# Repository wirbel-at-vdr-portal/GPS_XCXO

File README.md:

# About
Project goal is a small budget hobbyists GPS disciplined 10MHz XCXO with less than 0.01Hz freq offset at 10MHz using a GPS receiver with 1PPS output.

# Ingredients
- an cheap 10MHz OCXO with 0..4 volts V_control input, which has in it's voltage control range the center freq of 10.000000 MHz and CMOS or TTL output,
  costs at common market places ~15€. I use an CTI OSC5A2B02 OCXO based board. It needs to be modified however, to have a control voltage input instead of a potentiometer.
- an ESP32 devkit C V4, ~12€ (mine was ~8€)
- Arduino IDE with a few libs, 0€, but some efforts in/plus time/research.
- a GPS module with an 1 pulse per second output, in my case
  - Sparkfun GPS-17285 module (Neo-M9N)
  - Sparkfun GPS-14986 antenna
- a few electronic components
- an old 1.8 inch TFT based on St7735, i use the one with the large SD card slot, ~6€
- the PCB, design is here, ~25€ for 5 pieces.
- a 9..12volts DC power supply with ~1amp continously, - no costs. Everybody has such one laying around. Preferred with the 5.5mm 'DC connector', plus is inner.

# How it is working

- the 1PPS signal from the GNSS / GPS module triggers an interrupt routine, which resets a counter.
- the 10MHz signal is counted by the ESP32 specific hardware counter PCNT. Every 30000 counts, this counter fires a second ISR to count it's overflows.
  This ISR is called 333 times a second.
- if the gate time is over, we remember the current counter value (0..29999) as 'last_counter' and calculate the number of pulses: pulses = current_counter + overflows * 30000 - last_counter
- now, we can calculate the frequency: frequency = pulses / gate_time
- and the current frequency error in ppb: errorPPB = (measuredFreq - TARGET_FREQ) / (TARGET_FREQ / 1e9)
- as our OCXO is voltage controlled by 0..4volts, we need to generate a control voltage. We generate a 16-bit PWM, again using hardware counters of the ESP32.
- the pwm signal is RC filtered, we need to put a bit effort in this filter. We want more than 120dB frequency suppression for the PWM frequency.
- and finally, we somehow need to map an error in ppb to an PWM value. This job serves a digital filter with a bit brain, the Kalman filter.
- if the OCXO is learned, the program stores from time to time the current state

# Modification of the OCXO board
My OCXO board doesnt have a control voltage input. Instead, the input is wired to a potentiometer. The modified circuit is shown below.

NOTE: the original schematic was not done by me, see doc folder for original.

# Performance
- for my system, which is a very early breadboard-like assembly
- the algorithm needs time to adapt the OCXO, learn it's properties, so it's slow. Don't expect good results in less than two hours.
- there are still plenty of knobs to tune
- we need the OCXO control signal as clean as possible, so shielding and good RC filtering is mandatory.
- TODO
  - improve GPS quality (cheap module)
  - tune code, if GPS loss or invalid values.

| Running hh:mm:ss | abs(FreqOffset), Hz | PWM change 0..65535 | Uncertainty | comment |
| ----------- | ---------------- | ---------- | ----------- | -------- |
| 00:00:10    | 2.9              | 4751       | 490.8       |          |
| 00:00:20    | 1.8              | 2949       | 947.4       |          |
| 00:02:00    | 1.65             | 2703       | 264.0       |          |
| 00:03:40    | 0.51             |  836       | 205.7       |          |
| 00:12:00    | 0,216            |  354       |  10.7       |          |
| 00:28:40    | 0.058            |   95       |   2.65      |          |
| 00:45:20    | 0.013            |   21       |   2.31      |          |
| 01:02:00    | 0.002            |    3       |   1.9982    |          |
| 01:18:40    | 0.040            |    7       |   1.726     | GPS err  |
| 01:18:50    | 0                |    0       |   3.4488    | algo!    |
| 01:35:30    | 0.002            |    3       |   1.8489    | recover  |
| 01:52:10    | 0.001            |    2       |   1.3932    |          |

***NOTE NOTE NOTE:***

***This is work in progress. Everything still changes day by day. Success is optional, this is a fully fun based project.***

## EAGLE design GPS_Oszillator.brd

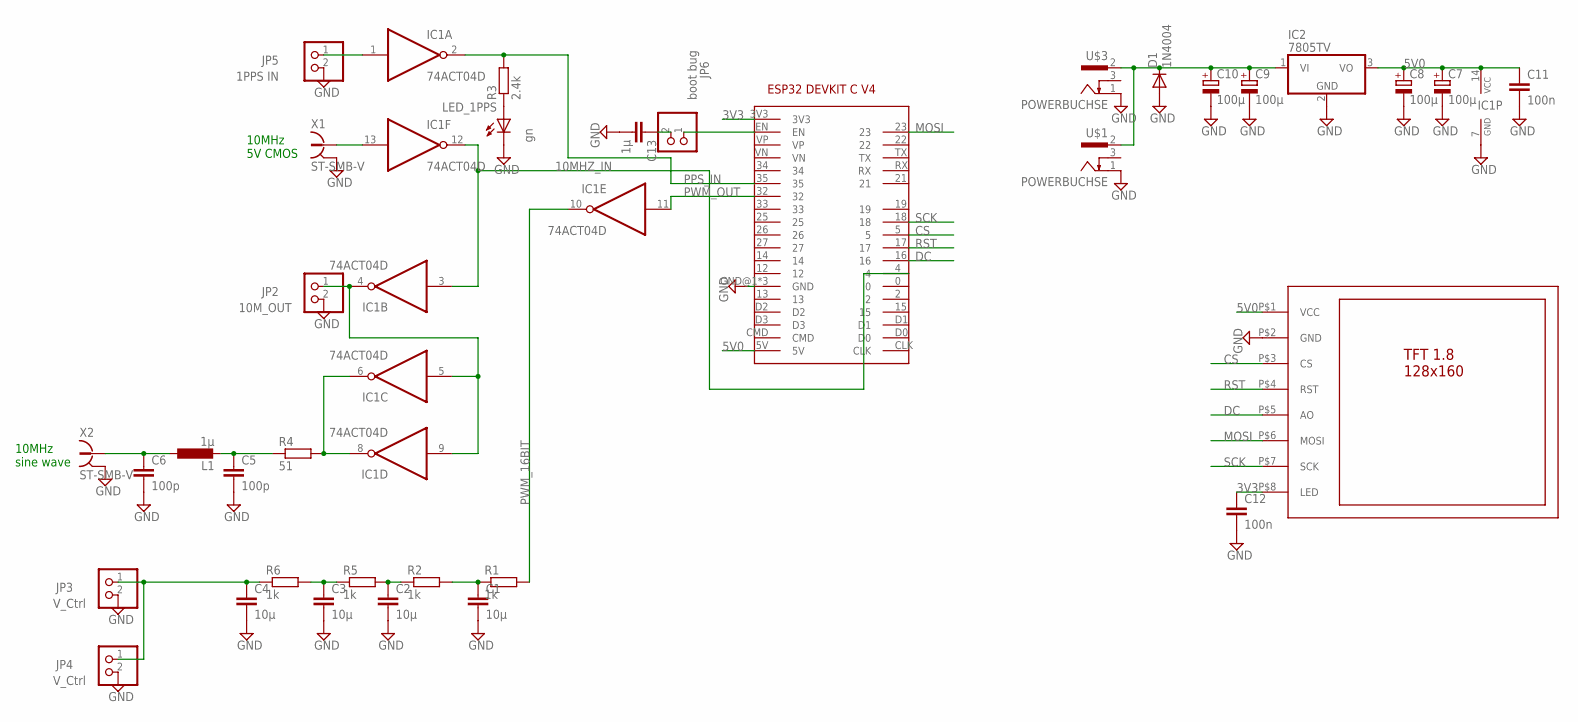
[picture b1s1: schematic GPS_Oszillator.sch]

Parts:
C1, C2, C3, C4: 10µ; C1206
C5, C6: 100p; C0805
C7, C8, C9, C10: 100µ; SANYO-OSCON_SMD_E7
C11, C12: 100n; C0805
C13: 1µ; C1210
D1: 1N4004; DO41-10
IC1: 74ACT04D; SO14
IC2: 7805TV; TO220V
JP2: 10M_OUT; 1X02
JP3, JP4: V_Ctrl; 1X02
JP5: 1PPS IN; 1X02
JP6: boot bug; 1X02
L1: 1µ; L1812
LED_1PPS: gn; CHIPLED_0805
R1, R2, R5, R6: 1k; R0805
R3: 2.4k; R0805
R4: 51; R0805
U$1, U$3: POWERBUCHSE
U$2: TFT_18
U$4: ESP32_DEVKITC_V4; ESP32_DEVKIT_C_V4
X1, X2: ST-SMB-V

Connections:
3V3: C12.1, U$2.P$8 (LED), U$4.3V3
5V0: C7.+, C8.+, C11.1, IC1.14 (VCC), IC2.3 (VO), U$2.P$1 (VCC), U$4.5V
10MHZ_IN: IC1.3 (I), IC1.12 (O), U$4.4
CS: U$2.P$3 (CS), U$4.5
DC: U$2.P$5 (AO), U$4.16
ESP32_EN: JP6.1, U$4.EN
GND: C1.2, C2.2, C3.2, C4.2, C5.2, C6.2, C7.-, C8.-, C9.-, C10.-, C11.2, C12.2, C13.2, D1.A, IC1.7 (GND), IC2.2 (GND), JP2.2, JP3.2, JP4.2, JP5.2, LED_1PPS.C, U$1.1 (2), U$2.P$2 (GND), U$3.1 (2), U$4.GND@1 (GND), U$4.GND@2 (GND), U$4.GND@3 (GND), X1.2, X1.3 (2), X1.4 (2), X1.5 (2), X2.2, X2.3 (2), X2.4 (2), X2.5 (2)
MOSI: U$2.P$6 (MOSI), U$4.23
unnamed: C3.1, R5.1, R6.2
unnamed: IC1.4 (O), IC1.5 (I), IC1.9 (I), JP2.1
unnamed: C2.1, R2.1, R5.2
unnamed: C13.1, JP6.2
unnamed: C1.1, R1.1, R2.2
unnamed: C4.1, JP3.1, JP4.1, R6.1
unnamed: IC1.1 (I), JP5.1
unnamed: LED_1PPS.A, R3.1
unnamed: C6.1, L1.1, X2.1
unnamed: C5.1, L1.2, R4.1
unnamed: IC1.6 (O), IC1.8 (O), R4.2
unnamed: C9.+, C10.+, D1.C, IC2.1 (VI), U$1.2 (1), U$3.2 (1)
unnamed: IC1.13 (I), X1.1
PPS_IN: IC1.2 (O), R3.2, U$4.35
PWM_16BIT: IC1.10 (O), R1.2
PWM_OUT: IC1.11 (I), U$4.32
RST: U$2.P$4 (RST), U$4.17
SCK: U$2.P$7 (SCK), U$4.18

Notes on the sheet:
10MHz 5V CMOS
10MHz sine wave

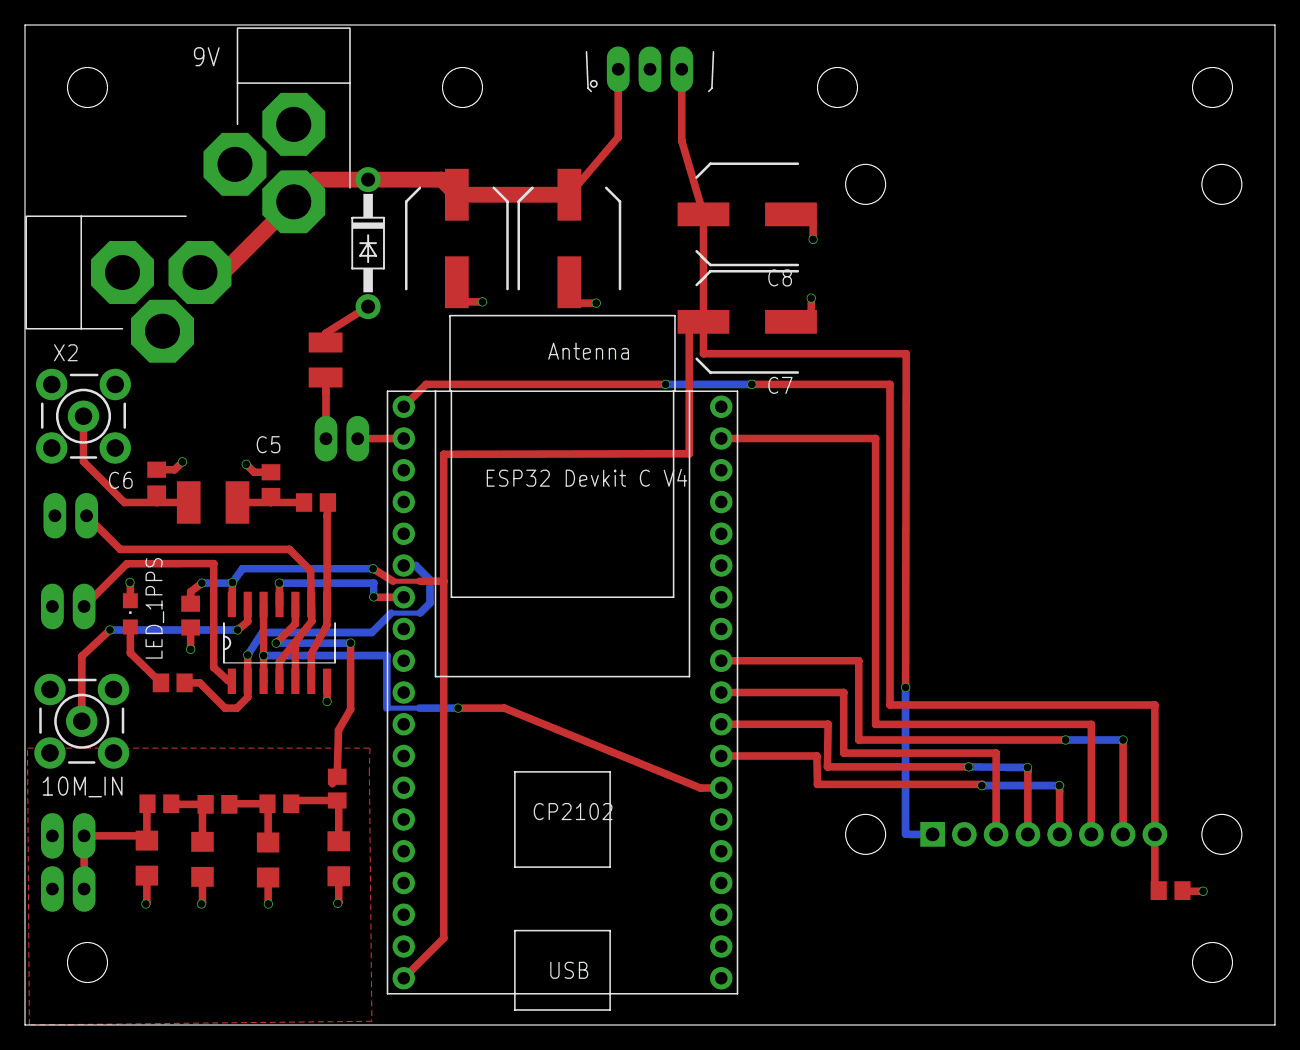
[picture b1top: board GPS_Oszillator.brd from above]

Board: 2 copper layers, 100.0 x 80.0 mm, 35 parts (0 on the bottom side), 26 nets.

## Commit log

2026-04-26 Add project goal to README.md
2026-04-27 Expand README with project details and ingredients
    Added project ingredients and notes about progress.
2026-04-29 Enhance README notes and thoughts formatting
    Updated the note section for clarity and emphasis. Reformatted thoughts for better readability.
2026-04-30 Change PWM filter
2026-05-02 Add first version of an Kalman Filter
    A Kalman filter is an iterative mathematical algorithm used to optimally estimate the state of a dynamic system (such as position or velocity) from a series of measurement errors. It was introduced b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
2026-05-02 Revise README for clarity and project details
    Updated project description and ingredients list for clarity. Added planned functionality and notes on project progress.
2026-05-02 Revise GPS module details in README
    Updated GPS module description and pricing.
2026-05-02 Fix typo in README regarding pulse calculation
2026-05-02 Update PWM generation description in README
2026-05-02 Update README with completed thoughts
    Strikethrough completed thoughts in README.
2026-05-02 fix folder structure
2026-05-02 update esp32 inputs.
2026-05-03 add second power connector and sort out drc errors
2026-05-04 add filter comparison in LTspice
2026-05-04 fix PCNT initialization and dont reset PCNT
    1. fix new initialization of PCNT Driver (v5.x) -> .low_limit = -1
    2. dont reset interrupt in OnOverflow(), just count.
    3. dont reset PCNT to zero in OnPPS() anymore. Instead, remember it's start value in loop(). This increases the counter accuracy.
    4. clean code.
2026-05-04 Increase accuracy of filter
    1. use double, instead of float in Kalman filter.
    2. begin playing with tuning variables
    3. add 1000sec measurement time
2026-05-05 save current setup.
2026-05-06 Revise README with updated project specifications
    Updated project details and specifications in README.md. Modified ingredient costs and clarified the working mechanism of the system.
2026-05-06 Enhance README with performance insights and TODOs
    Added performance section with details on OCXO adaptation and tuning.
2026-05-06 Add image to README and update project status note
2026-05-06 save current state
2026-05-08 Update project goal
    Updated project goal to specify a frequency offset of less than 0.01Hz instead of 0.5Hz.
2026-05-08 Update ingredients
2026-05-08 Update frequency calculation details
2026-05-08 Clarify counting process and ISR in README
    Refined explanation of the counting process and ISR calls.
2026-05-08 add image
    Added an image to the README and clarified project details.
2026-05-08 update README
    Added note about storing the current state of the OCXO.
2026-05-09 Fix reversed DC Jacks
2026-05-09 Increase diameter for inner pole of SMA connector.
2026-05-10 Add prototype image to README
    Added a prototype image to the README.
2026-05-12 adopt pwm to inverter gate
2026-05-13 write freq offset with 4 digits
2026-06-11 Add OCXO board modification details to README
    Added section on modification of the OCXO board, including a note about the original schematic and an image of the modified circuit.
2026-06-11 Add overview image
2026-06-11 sort files
